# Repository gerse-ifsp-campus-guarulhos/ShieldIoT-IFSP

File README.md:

# ShieldIoT-IFSP

Licença: GNU GPL 2

Autores: [Pedro Igor Borçatti da Silva](https://github.com/pedro-ibs)

This program is free software; you can redistribute it and/or
modify it under the terms of the GNU General Public License as
published by the Free Software Foundation; version 2 of the
License.

This program is distributed in the hope that it will be useful,
but WITHOUT ANY WARRANTY; without even the implied warranty of
MERCHANTABILITY or FITNESS FOR A PARTICULAR PURPOSE.  See the
GNU General Public License for more details.

---

O SHIELD IoT-IFSP é uma placa didática criada para a plataforma NodeMCU (ESP8266) de baixo custo, desenvolvida para o ensino de lógica de programação aplicada à robótica e Iot (internet das coisas), cujo principal objetivo é facilitar o ensino de lógica de programação.

Neste Repositório se encontra todos os arquivos necessários para o **DESENVOLVIMENTO e DOCUMENTAÇÃO** para a **Shield IoT**, não Existe exemplos e programas testes para essa versão embora versões anteriores já tenham sido testadas (e falharam em algum ponto) no entanto esta versão está aparentemente está tudo certo, ela leva correções eletrônicas e de layout.

Na pasta [PCB](PCB/) estão os arquivos para fabricação da placa, tanto o [GERBER](PCB/GERBER/) para fabricação manufaturada, e um [PDF](PCB/PCB.pdf) para fabricação manual por transferência térmica. Em [Documentação](Documentação/) temos os arquivos referente ao circuito, lá encontrado o BOM (lista de componentes, e em formato ods feito pelo libreoffice), O [esquema elétrico](Documentação/esquematico.pdf) em pdf e o [arquivos do kicad](Documentação/Circuito/) e suas dependências.

# Uso dos pinos atual:

# O que precisa ser feio
* Testar placa, e todos os periféricos disponíveis para uso;
* Fazer um manual como a [Shield Edu-IFSP ](https://github.com/gerse-ifsp-campus-guarulhos/ShieldEdu-IFSP);
* programa testes como o [Exemplo da Shield Edu-IFSP](https://github.com/gerse-ifsp-campus-guarulhos/ShieldEdu-IFSP/tree/master/Exemplos);
* Criar artigos e publicações.

# Versão antiga

Está é a foto da versão antiga da placa porem existe em algum lugar no gerse a mesma versão dos arquivos desse repositório construída por transferência térmica

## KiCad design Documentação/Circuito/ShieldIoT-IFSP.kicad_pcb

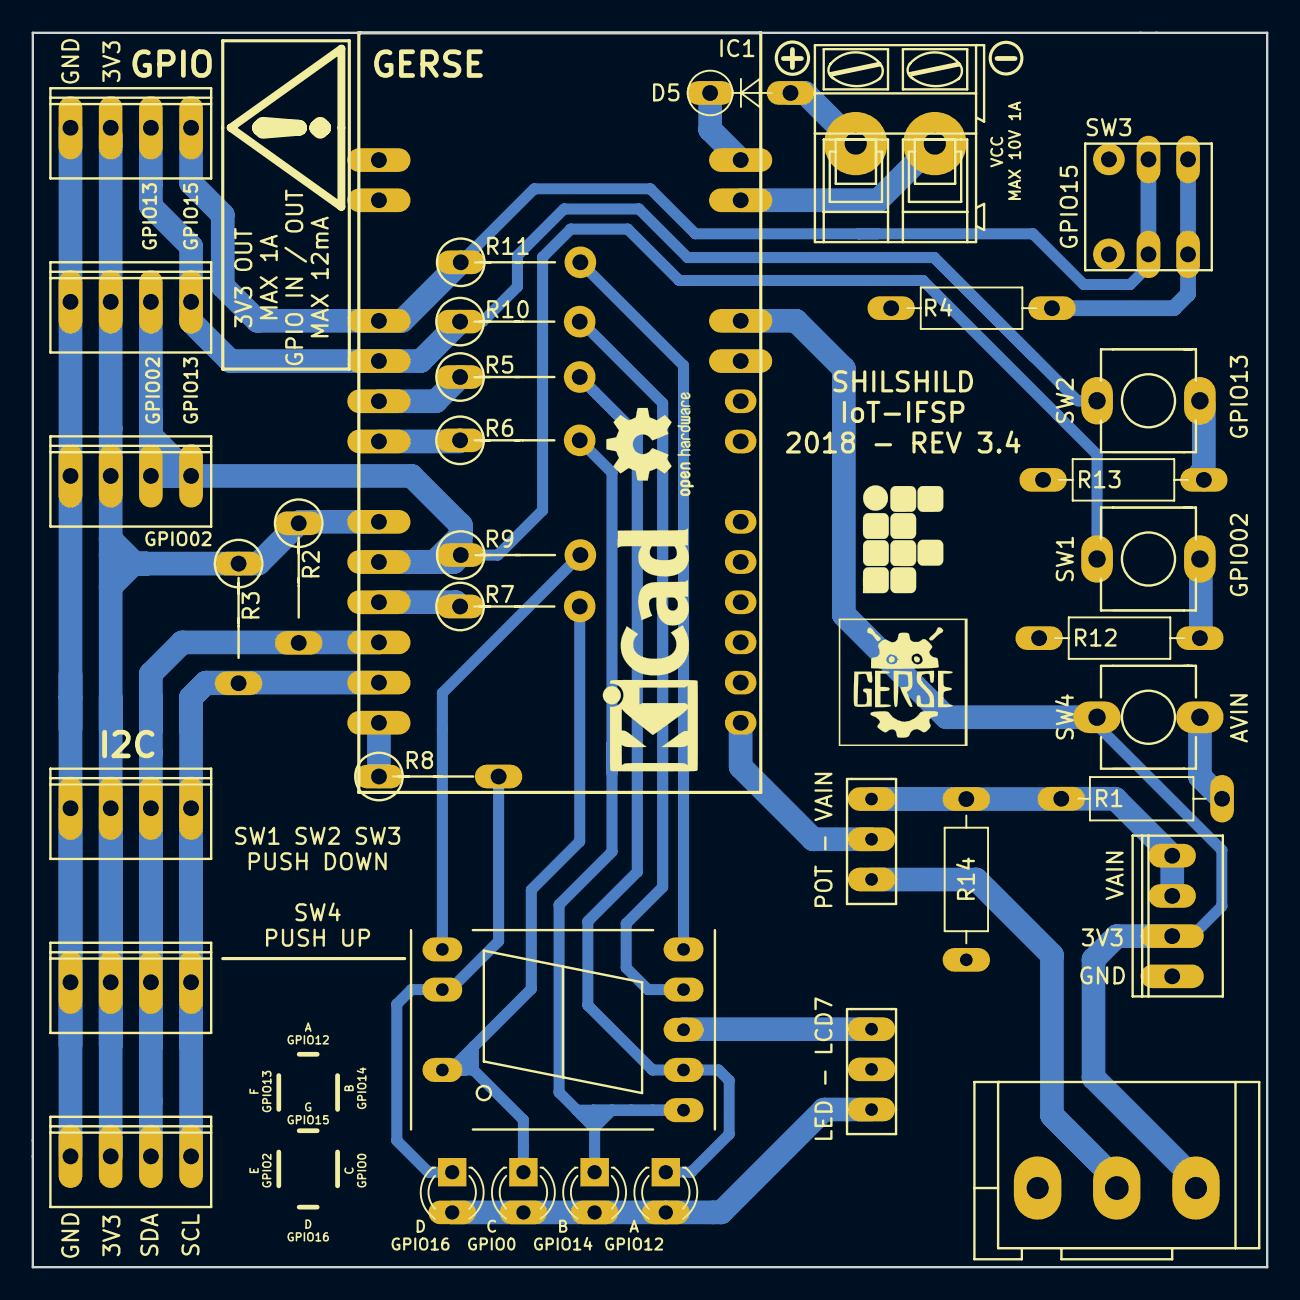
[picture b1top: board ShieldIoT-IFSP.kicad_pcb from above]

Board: 2 copper layers, 78.0 x 78.0 mm, 36 parts (0 on the bottom side), 28 nets.

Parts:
D1, D2, D3, D4: LED_ALT; LED_D3.0mm
D5: 1N4007; D_A-405_P5.08mm_Vertical_AnodeUp
IC1: NODEMCU
J1: VCC; AK300-2
J2, J3, J4: I2C; molex_2510
J5: VAIN; molex_2510
J6, J7, J8: OUT; molex_2510
JP1, JP2: JUMP3; Pin_Header_Straight_1x03
R1, R14: 100k; R_Axial_DIN0207_L6.3mm_D2.5mm_P10.16mm_Horizontal
R2, R3: 10K; Resistor_Vertical_RM7mm
R4, R12, R13: 10K; R_Axial_DIN0207_L6.3mm_D2.5mm_P10.16mm_Horizontal
R5, R6, R7, R8, R9, R10, R11: 470; Resistor_Vertical_RM7mm
RV1: R_POT; Potentiometer_Alps-RK16-single_largePads
SW1: BT1; MySW_PUSH_6mm_H4.3mm
SW2: BT2; MySW_PUSH_6mm_H4.3mm
SW3: SP6T; SW_PUSH_x2
SW4: BT3; MySW_PUSH_6mm_H4.3mm
U1: KCSA02-107; 7SegmentLED_LTS6760_LTS6780-2

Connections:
+3V3: IC1.3V3, J2.3, J3.3, J4.3, J5.3, J6.3, J7.3, J8.3, R2.1, R3.1, RV1.1, SW4.1
A: D4.1, R5.2, U1.7
ADC0: IC1.A0, JP1.2
B: D3.1, R6.2, U1.6
C: D2.1, R7.2, U1.4
D: D1.1, U1.2
E: R9.2, U1.1
Earth: IC1.GND, J1.2, J2.4, J3.4, J4.4, J5.4, J6.4, J7.4, J8.4, JP2.2, R4.2, R12.2, R13.2, R14.2, RV1.3
F: R10.2, U1.9
G: R11.2, U1.10
GPIO0: IC1.D3, R7.1
GPIO2: IC1.D4, J7.2, J8.1, J8.2, R9.1, SW1.1
GPIO12: IC1.D6, R5.1
GPIO13: IC1.D7, J6.2, J7.1, R10.1, SW2.1
GPIO14: IC1.D5, R6.1
GPIO15: IC1.D8, J6.1, R11.1, SW3.2, SW3.5
LCD7: JP2.3, U1.8
LED: D1.2, D2.2, D3.2, D4.2, JP2.1
unnamed: D5.2, J1.1
unnamed: R1.1, SW4.2
unnamed: R4.1, SW3.3, SW3.4
unnamed: R12.1, SW1.2
unnamed: R13.1, SW2.2
POT: JP1.1, RV1.2
SCL: IC1.D1, J2.1, J3.1, J4.1, R3.2
SDA: IC1.D2, J2.2, J3.2, J4.2, R2.2
VAIN: J5.1, J5.2, JP1.3, R1.2, R14.1
VCC: D5.1, IC1.VIN

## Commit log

2019-07-12 SHIELDIoT-IFSP
2019-07-12 arrumando linkis
2019-07-12 arrumando links
2019-07-15 att REDAME
